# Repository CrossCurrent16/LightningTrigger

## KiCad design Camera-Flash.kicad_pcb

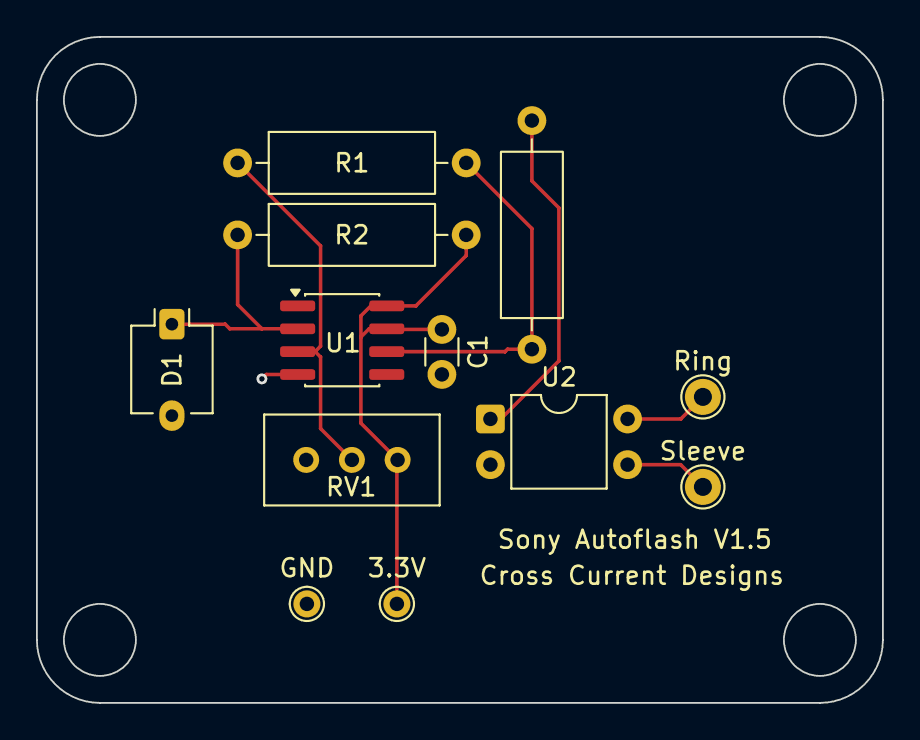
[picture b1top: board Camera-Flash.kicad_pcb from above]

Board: 2 copper layers, 47.0 x 37.0 mm, 12 parts (0 on the bottom side), 8 nets.

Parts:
3.3V: TestPoint_THTPad_D1.5mm_Drill0.7mm
C1: 1uF; C_Disc_D3.0mm_W1.6mm_P2.50mm
D1: BPW34; Osram_DIL2_4.3x4.65mm_P5.08mm
GND: TestPoint_THTPad_D1.5mm_Drill0.7mm
R1: 100k; R_Axial_DIN0309_L9.0mm_D3.2mm_P12.70mm_Horizontal
R2: 10k-100k; R_Axial_DIN0309_L9.0mm_D3.2mm_P12.70mm_Horizontal
R3: 470 OHM; R_Axial_DIN0309_L9.0mm_D3.2mm_P12.70mm_Horizontal
RV1: R_Potentiometer_Trim_US; Potentiometer_Bourns_3296W_Vertical
Ring: TestPoint_THTPad_D2.0mm_Drill1.0mm
Sleeve: TestPoint_THTPad_D2.0mm_Drill1.0mm
U1: TLV3501AID; SOIC-8_3.9x4.9mm_P1.27mm
U2: LTV-817; DIP-4_W7.62mm

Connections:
+3.3V: 3.3V.1, C1.2, R2.2, RV1.1, U1.7 (V+), U1.8 (SHDN)
GND: C1.1, D1.2 (A), GND.1 (GND), RV1.3, U1.4 (V-), U2.2
unnamed: D1.1 (K), R2.1, U1.2 (-)
unnamed: Ring.1, U2.4
unnamed: Sleeve.1, U2.3
unnamed: R1.2, R3.1, U1.6
unnamed: R3.2, U2.1
unnamed: R1.1, RV1.2, U1.3 (+)
